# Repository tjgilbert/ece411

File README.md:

## ECE411 Practicum Project

**Project Focus:** Inductive Charging

**Team 10:** Jeff Brown, Katie Dahn, Tyler Gilbert, Jann Messer

*  [Project Wiki] (https://github.com/tjgilbert/ece411/wiki)

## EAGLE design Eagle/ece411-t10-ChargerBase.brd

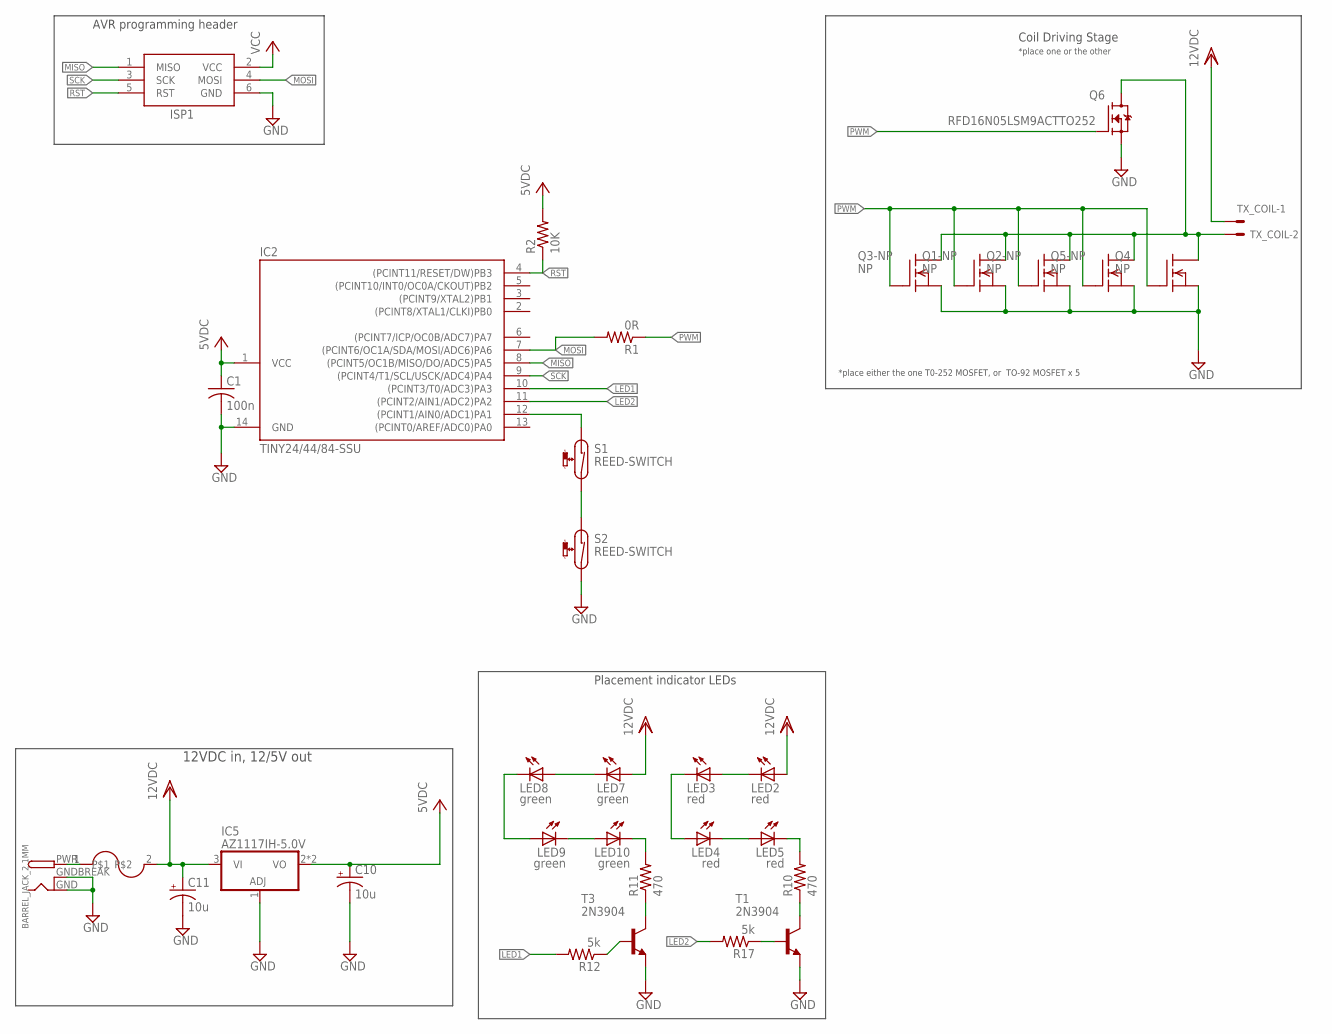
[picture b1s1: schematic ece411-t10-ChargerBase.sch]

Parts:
BARREL_JACK_2.1MM: DCBARRELPTH; DCJACK_2MM_PTH
C1: 100n; C0805
C10, C11: 10u; E2-5
IC2: TINY24/44/84-SSU; SOIC14
IC5: AZ1117IH-5.0V; SOT223
ISP1: AVRISP-6; AVRISP
LED2, LED3, LED4, LED5: red; CHIPLED_0805
LED7, LED8, LED9, LED10: green; CHIPLED_0805
Q1-NP, Q2-NP, Q3-NP, Q4, Q5-NP: NP; TO-92
Q6: RFD16N05LSM9ACTTO252; TO252
R1: 0R; R0805
R2: 10K; R0805
R10, R11: 470; R0805
R12, R17: 5k; R0805
S1, S2: REED-SWITCH; MK6-6
T1, T3: 2N3904; TO92
TX_COIL: 22-23-2021
U$1: LITTLEFUSE

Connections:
DRAIN: Q1-NP.3 (D), Q2-NP.3 (D), Q3-NP.3 (D), Q4.3 (D), Q5-NP.3 (D), Q6.3 (D), TX_COIL.2
GND: BARREL_JACK_2.1MM.GND, BARREL_JACK_2.1MM.GNDBREAK, C1.2, C10.-, C11.-, IC2.14 (GND), IC5.1 (ADJ), ISP1.6 (GND), Q1-NP.1 (S), Q2-NP.1 (S), Q3-NP.1 (S), Q4.1 (S), Q5-NP.1 (S), Q6.2 (S), S2.2, T1.3 (E), T3.3 (E)
LED1: IC2.10 ((PCINT3/T0/ADC3)PA3), R12.2
LED2: IC2.11 ((PCINT2/AIN1/ADC2)PA2), R17.2
MISO: IC2.8 ((PCINT5/OC1B/MISO/DO/ADC5)PA5), ISP1.1 (MISO)
MOSI: IC2.7 ((PCINT6/OC1A/SDA/MOSI/ADC6)PA6), ISP1.4 (MOSI), R1.2
unnamed: R11.1, T3.1 (C)
unnamed: LED10.C, R11.2
unnamed: BARREL_JACK_2.1MM.PWR, U$1.1
unnamed: R17.1, T1.2 (B)
unnamed: R10.1, T1.1 (C)
unnamed: LED5.C, R10.2
unnamed: LED2.C, LED3.A
unnamed: LED3.C, LED4.A
unnamed: LED4.C, LED5.A
unnamed: S1.2, S2.1
unnamed: LED7.C, LED8.A
unnamed: LED8.C, LED9.A
unnamed: LED9.C, LED10.A
unnamed: R12.1, T3.2 (B)
PIN12: IC2.12 ((PCINT1/AIN0/ADC1)PA1), S1.1
PWM: Q1-NP.2 (G), Q2-NP.2 (G), Q3-NP.2 (G), Q4.2 (G), Q5-NP.2 (G), Q6.1 (G), R1.1
RST: IC2.4 ((PCINT11/RESET/DW)PB3), ISP1.5 (RST), R2.1
SCK: IC2.9 ((PCINT4/T1/SCL/USCK/ADC4)PA4), ISP1.3 (SCK)
VCC: C1.1, C10.+, IC2.1 (VCC), IC5.2 (VO), IC5.4 (VO), ISP1.2 (VCC), R2.2
VDD: C11.+, IC5.3 (VI), LED2.A, LED7.A, TX_COIL.1, U$1.2

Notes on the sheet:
AVR programming header
12VDC in, 12/5V out
Coil Driving Stage
Placement indicator LEDs
*place one or the other
*place either the one T0-252 MOSFET, or TO-92 MOSFET x 5

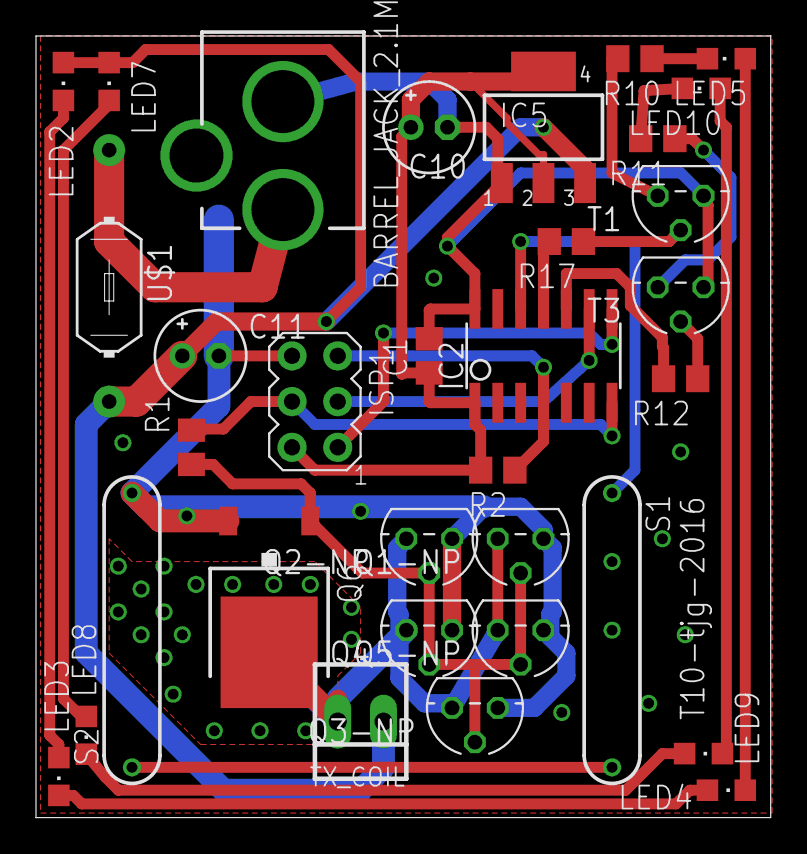
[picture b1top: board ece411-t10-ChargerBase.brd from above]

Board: 2 copper layers, 40.8 x 43.4 mm, 33 parts (0 on the bottom side), 26 nets.

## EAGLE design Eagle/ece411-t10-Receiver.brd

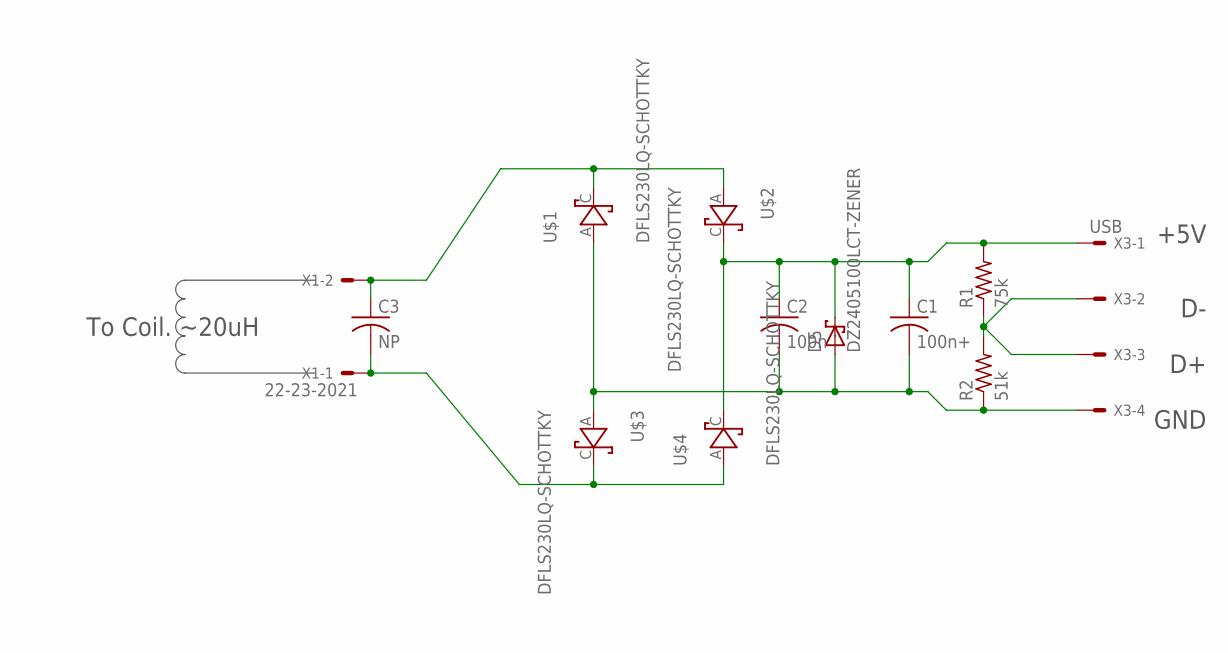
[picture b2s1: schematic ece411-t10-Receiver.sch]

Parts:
C1: 100n+; C0805
C2: 100n; C0805
C3: NP; C0805
D5: DZ2405100LCT-ZENER; ZENER_PWR_PKG
R1: 75k; R0805
R2: 51k; R0805
U$1, U$2, U$3, U$4: DFLS230LQ-SCHOTTKY; PWRDI123
X1: 22-23-2021
X3: USB; 22-23-2041

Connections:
5V: C1.1, C2.1, D5.C, R1.2, U$2.C, U$4.C, X3.1
GND: C1.2, C2.2, D5.A, R2.1, U$1.A, U$3.A, X3.4
unnamed: C3.1, U$1.C, U$2.A, X1.2
unnamed: C3.2, U$3.C, U$4.A, X1.1
unnamed: R1.1, R2.2, X3.2, X3.3

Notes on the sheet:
To Coil. ~20uH
+5V
GND

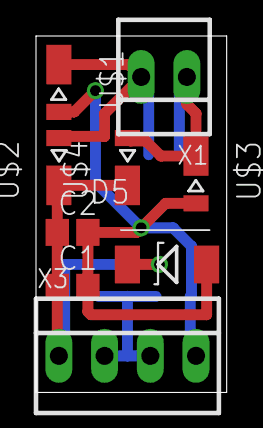
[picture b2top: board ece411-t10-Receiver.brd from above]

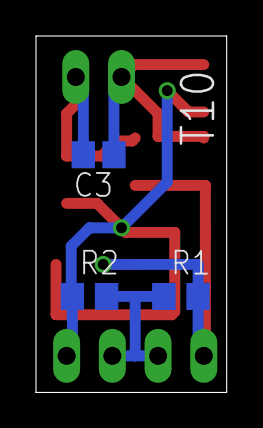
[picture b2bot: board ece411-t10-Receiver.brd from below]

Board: 2 copper layers, 10.6 x 19.8 mm, 12 parts (3 on the bottom side), 5 nets.

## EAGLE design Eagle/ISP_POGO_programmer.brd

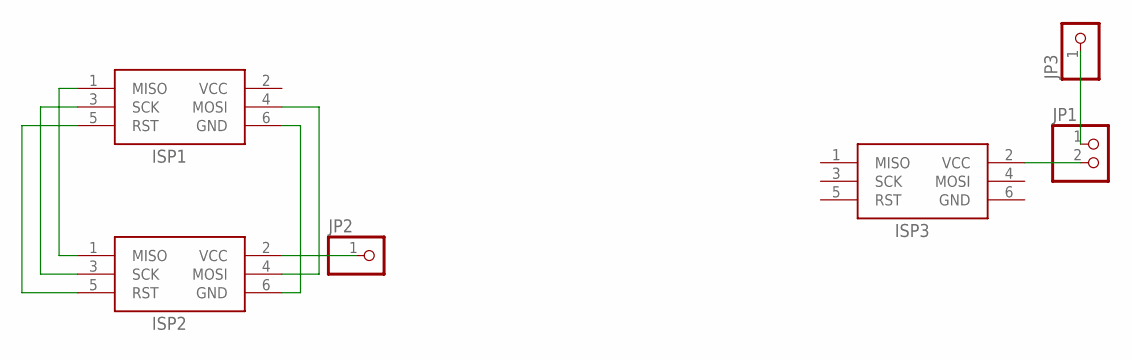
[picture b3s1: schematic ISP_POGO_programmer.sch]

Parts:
ISP1, ISP2, ISP3: AVRISP-6; AVRISP
JP1: PINHD-1X2; 1X02
JP2, JP3: PINHD-1X1; 1X01

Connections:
GND: ISP3.6 (GND)
unnamed: ISP1.1 (MISO), ISP2.1 (MISO)
unnamed: ISP1.3 (SCK), ISP2.3 (SCK)
unnamed: ISP1.5 (RST), ISP2.5 (RST)
unnamed: ISP1.6 (GND), ISP2.6 (GND)
unnamed: ISP1.4 (MOSI), ISP2.4 (MOSI)
unnamed: ISP3.2 (VCC), JP1.2
unnamed: JP1.1, JP3.1
unnamed: ISP2.2 (VCC), JP2.1
VCC: ISP1.2 (VCC)

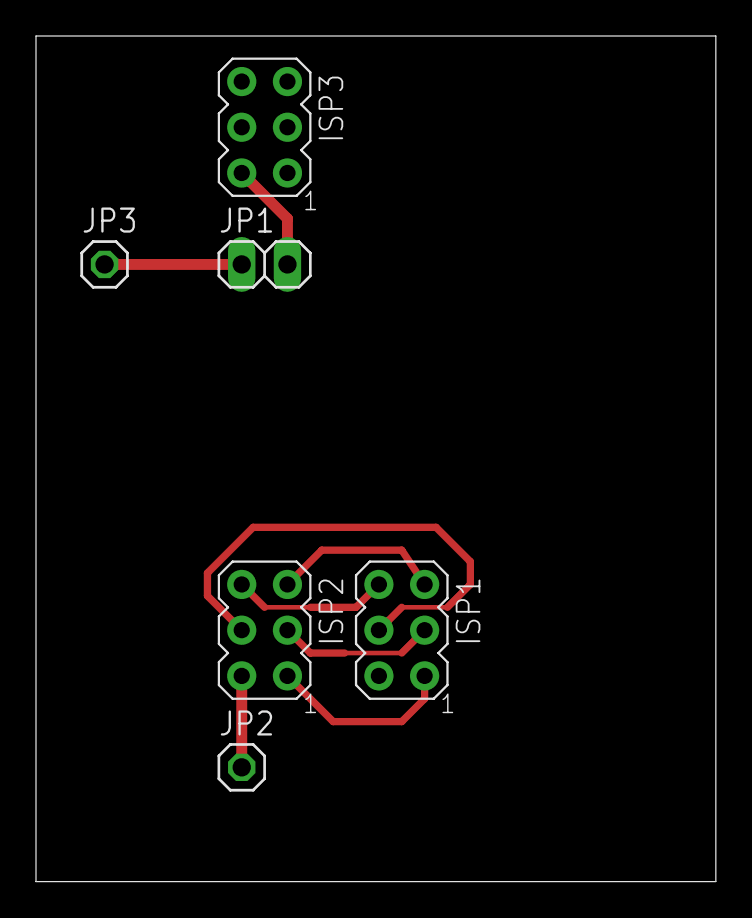
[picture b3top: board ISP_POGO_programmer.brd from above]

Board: 2 copper layers, 37.8 x 47.0 mm, 6 parts (0 on the bottom side), 8 nets.

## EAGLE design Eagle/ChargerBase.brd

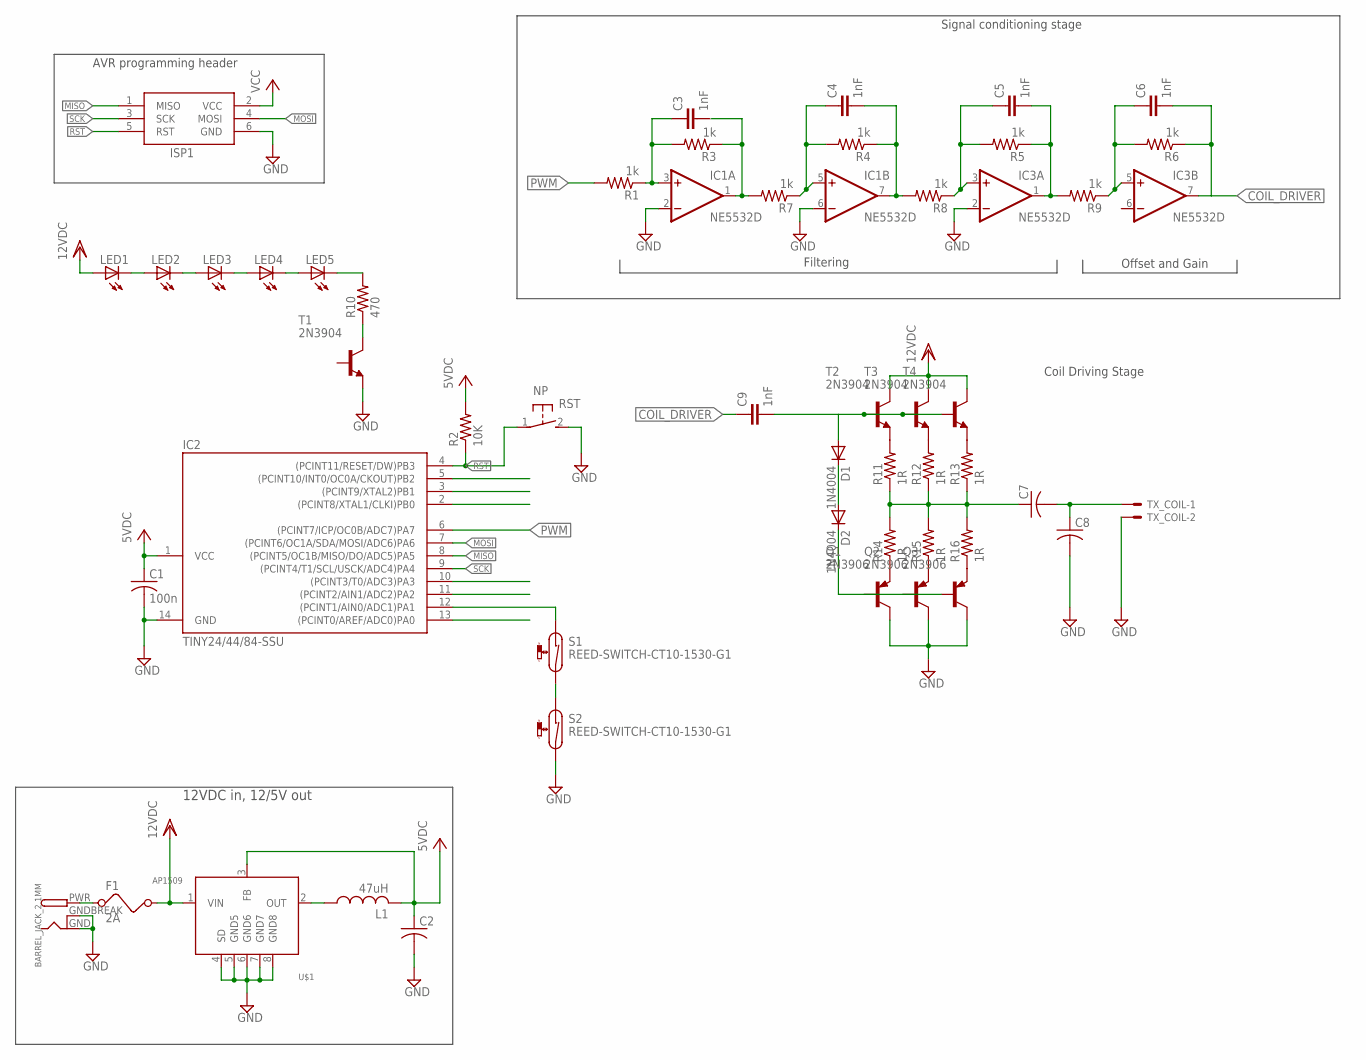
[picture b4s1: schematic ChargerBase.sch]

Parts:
BARREL_JACK_2.1MM: DCBARRELPTH; DCJACK_2MM_PTH
C1: 100n; C0805
C2: C-US025-040X050; C025-040X050
C3, C4, C5, C6, C9: 1nF; C0805
C7, C8: C-US050-025X075; C050-025X075
D1, D2: 1N4004; DO41-10
F1: 2A; FUSE
IC1, IC3: NE5532D; SO08
IC2: TINY24/44/84-SSU; SOIC14
ISP1: AVRISP-6; AVRISP
L1: 47uH; 0207/7
LED1, LED2, LED3, LED4, LED5: LEDCHIPLED_0805; CHIPLED_0805
NP: RST; DTSM-3
Q1, Q2, Q3: 2N3906; TO92
R1, R3, R4, R5, R6, R7, R8, R9: 1k; R0805
R2: 10K; R0805
R10: 470; R0805
R11, R12, R13, R14, R15, R16: 1R; R0805
S1, S2: REED-SWITCH-CT10-1530-G1; CT10-G1
T1, T2, T3, T4: 2N3904; TO92
TX_COIL: 22-23-2021
U$1: AP1509; SOP08

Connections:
COIL_DRIVER: C6.2, C9.1, IC3.7 (OUT), R6.1
GND: BARREL_JACK_2.1MM.GND, BARREL_JACK_2.1MM.GNDBREAK, C1.2, C2.2, C8.2, IC1.2 (-IN), IC1.6 (-IN), IC2.14 (GND), IC3.2 (-IN), ISP1.6 (GND), NP.2, Q1.1 (C), Q2.1 (C), Q3.1 (C), S2.2, T1.3 (E), TX_COIL.2, U$1.4 (SD), U$1.5 (GND5), U$1.6 (GND6), U$1.7 (GND7), U$1.8 (GND8)
MISO: IC2.8 ((PCINT5/OC1B/MISO/DO/ADC5)PA5), ISP1.1 (MISO)
MOSI: IC2.7 ((PCINT6/OC1A/SDA/MOSI/ADC6)PA6), ISP1.4 (MOSI)
unnamed: C3.1, IC1.3 (+IN), R1.1, R3.2
unnamed: L1.1, U$1.2 (OUT)
unnamed: R11.2, T2.3 (E)
unnamed: BARREL_JACK_2.1MM.PWR, F1.1
unnamed: IC1.1 (OUT), R3.1, R7.2
unnamed: C4.1, IC1.5 (+IN), R4.2, R7.1
unnamed: C4.2, IC1.7 (OUT), R4.1, R8.2
unnamed: C5.1, IC3.3 (+IN), R5.2, R8.1
unnamed: C5.2, IC3.1 (OUT), R5.1, R9.2
unnamed: C6.1, IC3.5 (+IN), R6.2, R9.1
unnamed: R12.2, T3.3 (E)
unnamed: LED1.C, LED2.A
unnamed: LED2.C, LED3.A
unnamed: LED3.C, LED4.A
unnamed: LED4.C, LED5.A
unnamed: LED5.C, R10.2
unnamed: S1.2, S2.1
unnamed: R13.2, T4.3 (E)
unnamed: Q1.3 (E), R14.1
unnamed: Q2.3 (E), R15.1
unnamed: Q3.3 (E), R16.1
unnamed: C7.1, R11.1, R12.1, R13.1, R14.2, R15.2, R16.2
unnamed: C9.2, D1.A, T2.2 (B), T3.2 (B), T4.2 (B)
unnamed: D1.C, D2.A
unnamed: C7.2, C8.1, TX_COIL.1
unnamed: D2.C, Q1.2 (B), Q2.2 (B), Q3.2 (B)
PIN10: IC2.10 ((PCINT3/T0/ADC3)PA3)
PIN11: IC2.11 ((PCINT2/AIN1/ADC2)PA2)
PIN12: IC2.12 ((PCINT1/AIN0/ADC1)PA1), S1.1
PIN13: IC2.13 ((PCINT0/AREF/ADC0)PA0)
PWM: IC2.6 ((PCINT7/ICP/OC0B/ADC7)PA7), R1.2
RST: IC2.4 ((PCINT11/RESET/DW)PB3), ISP1.5 (RST), NP.1, R2.1
SCK: IC2.9 ((PCINT4/T1/SCL/USCK/ADC4)PA4), ISP1.3 (SCK)
V+: IC1.8 (V+), IC3.8 (V+)
V-: IC1.4 (V-), IC3.4 (V-)
VCC: C1.1, C2.1, IC2.1 (VCC), ISP1.2 (VCC), L1.2, R2.2, U$1.3 (FB)
VDD: F1.2, LED1.A, T2.1 (C), T3.1 (C), T4.1 (C), U$1.1 (VIN)

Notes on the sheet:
AVR programming header
12VDC in, 12/5V out
Filtering
Offset and Gain
Coil Driving Stage
Signal conditioning stage

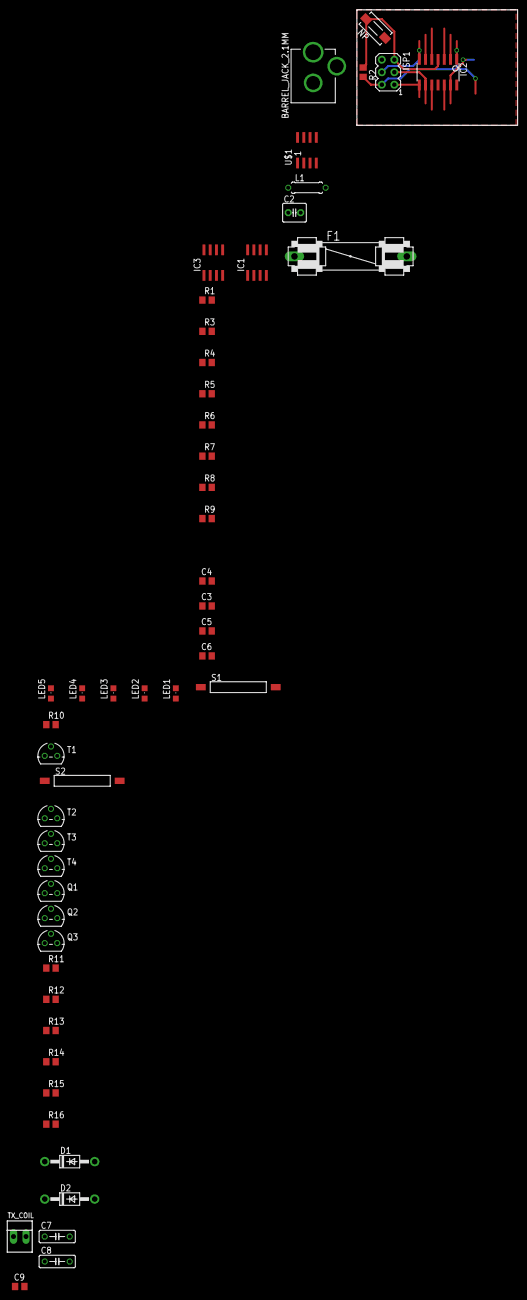
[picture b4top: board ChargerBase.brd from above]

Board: 2 copper layers, 32.7 x 23.5 mm, 51 parts (1 on the bottom side), 38 nets.

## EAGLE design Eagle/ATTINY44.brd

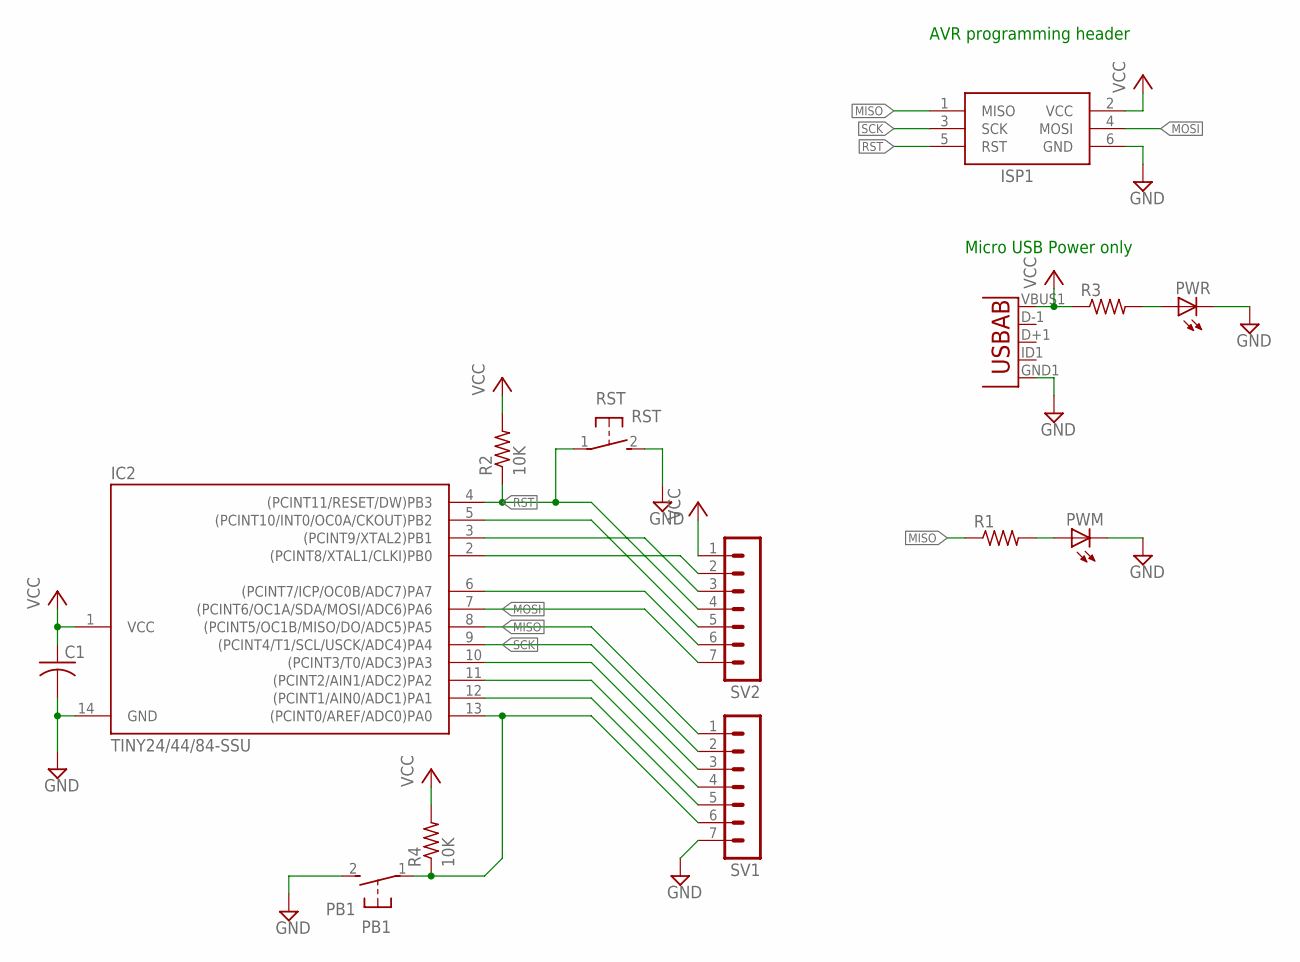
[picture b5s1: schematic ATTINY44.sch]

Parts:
C1: C-USC0805; C0805
IC2: TINY24/44/84-SSU; SOIC14
ISP1: AVRISP-6; AVRISP
PB1: PB1; DTSM-3
PWM: LEDCHIPLED_0805; CHIPLED_0805
PWR: LEDCHIPLED_0805; CHIPLED_0805
R1, R3: R-US_R0805; R0805
R2, R4: 10K; R0805
RST: RST; DTSM-3
SV1, SV2: MA07-1
U1: USB""; USB-MICRO-SMD

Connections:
GND: C1.2, IC2.14 (GND), ISP1.6 (GND), PB1.2, PWM.C, PWR.C, RST.2, SV1.7, U1.GND1 (GND)
MISO: IC2.8 ((PCINT5/OC1B/MISO/DO/ADC5)PA5), ISP1.1 (MISO), R1.1, SV1.1
MOSI: IC2.7 ((PCINT6/OC1A/SDA/MOSI/ADC6)PA6), ISP1.4 (MOSI), SV2.7
unnamed: PWR.A, R3.2
unnamed: PWM.A, R1.2
unnamed: IC2.2 ((PCINT8/XTAL1/CLKI)PB0), SV2.2
unnamed: IC2.3 ((PCINT9/XTAL2)PB1), SV2.3
unnamed: IC2.5 ((PCINT10/INT0/OC0A/CKOUT)PB2), SV2.5
unnamed: IC2.6 ((PCINT7/ICP/OC0B/ADC7)PA7), SV2.6
PIN10: IC2.10 ((PCINT3/T0/ADC3)PA3), SV1.3
PIN11: IC2.11 ((PCINT2/AIN1/ADC2)PA2), SV1.4
PIN12: IC2.12 ((PCINT1/AIN0/ADC1)PA1), SV1.5
PIN13: IC2.13 ((PCINT0/AREF/ADC0)PA0), PB1.1, R4.1, SV1.6
RST: IC2.4 ((PCINT11/RESET/DW)PB3), ISP1.5 (RST), R2.1, RST.1, SV2.4
SCK: IC2.9 ((PCINT4/T1/SCL/USCK/ADC4)PA4), ISP1.3 (SCK), SV1.2
VCC: C1.1, IC2.1 (VCC), ISP1.2 (VCC), R2.2, R3.1, R4.2, SV2.1, U1.VBUS1 (VBUS)

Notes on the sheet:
AVR programming header
Micro USB Power only

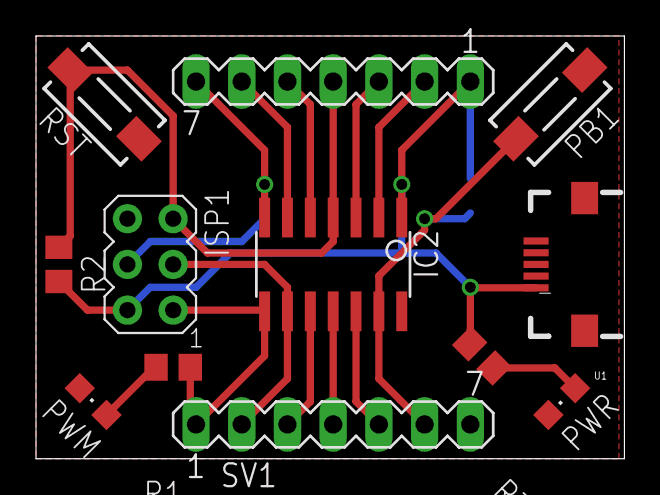
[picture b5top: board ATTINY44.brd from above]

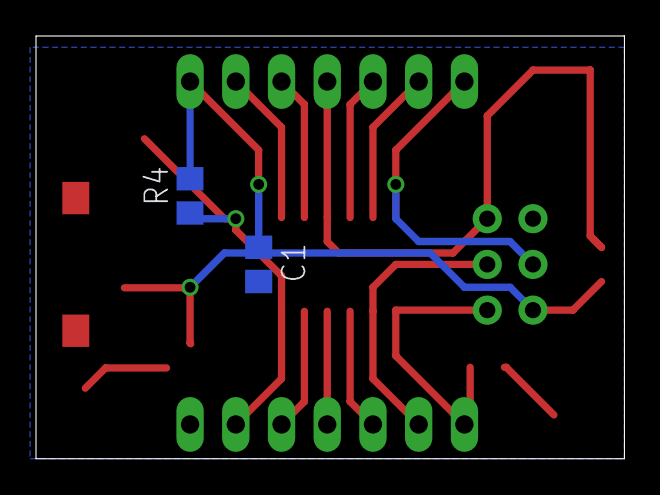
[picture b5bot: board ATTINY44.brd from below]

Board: 2 copper layers, 32.7 x 23.5 mm, 14 parts (2 on the bottom side), 16 nets.

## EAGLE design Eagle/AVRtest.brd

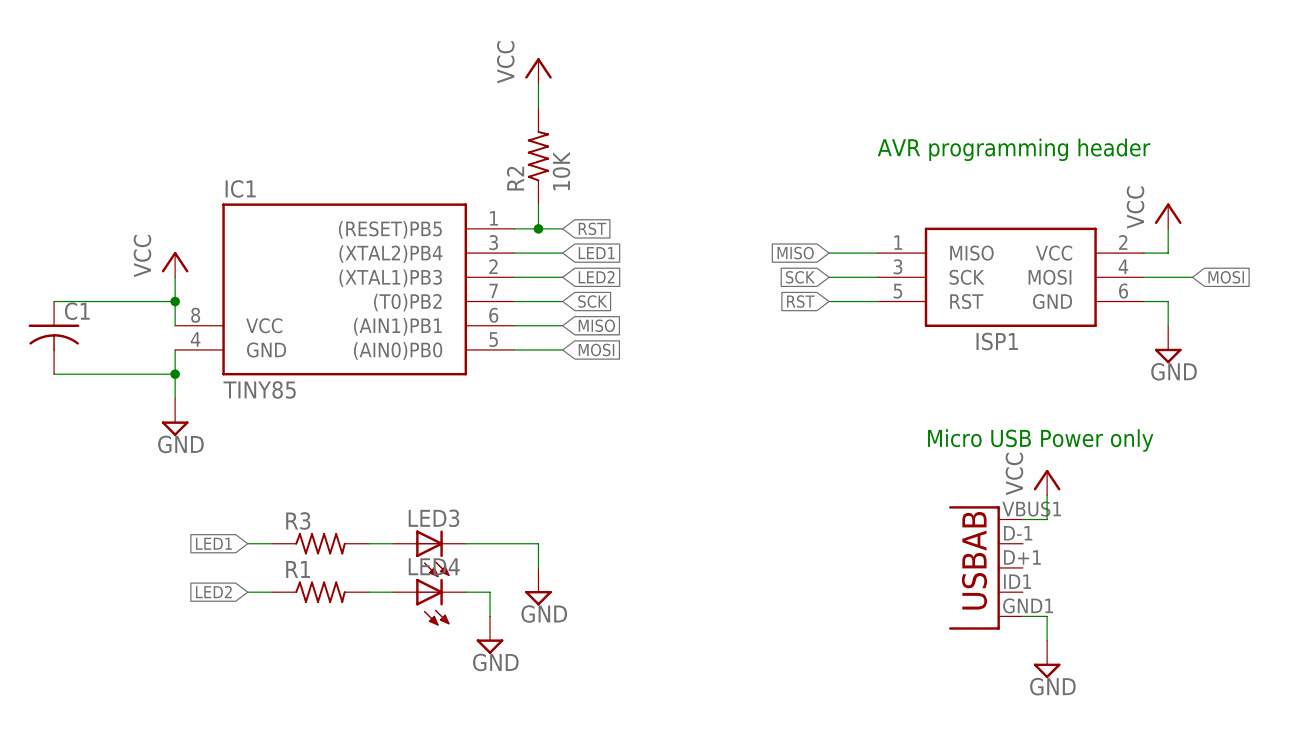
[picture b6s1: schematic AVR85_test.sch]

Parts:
C1: C-USC0805; C0805
IC1: TINY85; SOIC8
ISP1: AVRISP-6; AVRISP
LED3, LED4: LEDCHIPLED_0805; CHIPLED_0805
R1, R3: R-US_R0805; R0805
R2: 10K; R0805
U1: USB""; USB-MICRO-SMD

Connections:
GND: C1.2, IC1.4 (GND), ISP1.6 (GND), LED3.C, LED4.C, U1.GND1 (GND)
LED1: IC1.3 ((XTAL2)PB4), R3.1
LED2: IC1.2 ((XTAL1)PB3), R1.1
MISO: IC1.6 ((AIN1)PB1), ISP1.1 (MISO)
MOSI: IC1.5 ((AIN0)PB0), ISP1.4 (MOSI)
unnamed: LED3.A, R3.2
unnamed: LED4.A, R1.2
RST: IC1.1 ((RESET)PB5), ISP1.5 (RST), R2.1
SCK: IC1.7 ((T0)PB2), ISP1.3 (SCK)
VCC: C1.1, IC1.8 (VCC), ISP1.2 (VCC), R2.2, U1.VBUS1 (VBUS)

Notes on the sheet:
AVR programming header
Micro USB Power only

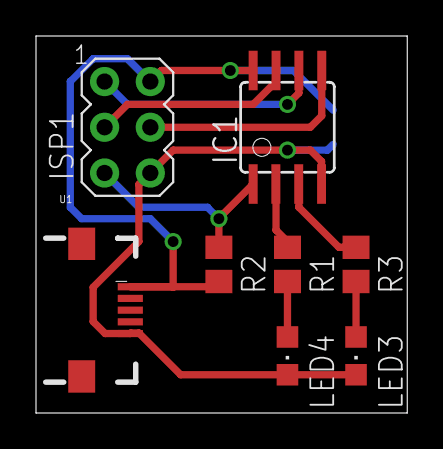
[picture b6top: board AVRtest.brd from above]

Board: 2 copper layers, 20.6 x 20.9 mm, 9 parts (1 on the bottom side), 10 nets.

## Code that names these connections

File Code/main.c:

#include <stdio.h>
#include <avr/io.h>
#include <avr/interrupt.h>
#include <util/delay.h>
#include <avr/power.h>

void initIO(void) {
/*       PDIP/SOIC Pinout:
                                VCC|1 14|GND
            (PCINT8/XTAL1/CLKI) PB0|2 13|PA0 (ADC0/AREF/PCINT0)
                 (PCINT9/XTAL2) PB1|3 12|PA1 (ADC1/AIN0/PCINT1)
             (PCINT11/RESET/dW) PB3|4 11|PA2 (ADC2/AIN1/PCINT2)
      (PCINT10/INT0/OC0A/CKOUT) PB2|5 10|PA3 (ADC3/T0/PCINT3)
         (PCINT7/ICP/OC0B/ADC7) PA7|6  9|PA4 (ADC4/USCK/SCL/T1/PCINT4)
 (PCINT6/OC1A/SDA/MOSI/DI/ADC6) PA6|7  8|PA5 (ADC5/DO/MISO/OC1B/PCINT5)
*/
    
 //Initial setup:
 // MCUCR = 0x40; // Uncomment to disable internal pull ups
    DDRA =  0b11111111; //Port A data direction register [DDA7:DDA0] (0=input 1=output)
    DDRB =  0xFF; //Port B data direction register [DDB3:DDB0] (0=input 1=output)
    PORTA = 0b00000000; //Port A data register [PORTA7:PORTA0]
    PORTB = 0b00000000; //Port B data register [PORTA3:PORTB0]
    
    
//PWM SETUP
    
    OSCCAL = 0x7F; // set internal oscilator frequency. The two values overlap, ie. 0x7F > 0x80
    clock_prescale_set(0);  // default is /8.. (0) = /1 , (1)= /2, (8)=/256
    
    //DDRA|=(1<<PA6);
    
    TCCR1A = _BV(COM1A1) | _BV(WGM11);     //TCCR1A = COM1A1 COM1A0 COM1B1 COM1B0 – – WGM11 WGM10
   
    TCCR1B = _BV(CS10) | _BV(WGM12) | _BV(WGM13);
        ICR1 = 80;
        OCR1A = 40;
        OCR1B = 40;
    
    
    
    TCCR0A = _BV(COM0B1) /*| _BV(COM0B0)*/ | _BV(WGM02)|_BV(WGM01) | _BV(WGM00);
    
    TCCR0B = _BV(CS00) ; //No prescaling - toggle mode?
    
    OCR0A =10;
    OCR0B = 50;
}

int main(void) {
    
	initIO();

    
	while (1) {
	/*
        do nothing
    */
     }
	return 0; // never reached
}

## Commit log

2016-10-12 Added subfolders
2016-10-12 Revert "Added subfolders"
    This reverts commit 49b2c9061165242376cadfb0a99d3f012eb89102.
2016-10-12 Added AVR test board schematics
2016-10-16 Commit Test
2016-10-16 Added ATTINY44 breakout board
2016-10-17 Waveform and FFT from inductive tap on transmit coil.
2016-10-17 Test setup, reference photo
2016-10-18 Made folders
2016-10-23 added code section
2016-10-23 Added some initialization code
2016-10-23 deleted eagle autosave files and added to .gitignore
2016-10-24 uploaded requirements document
2016-10-24 Completed PDS
2016-10-24 Uploaded PDS pdf
2016-10-25 Uploaded HW3 V1.2
2016-10-25 PDS rev 1.3
2016-10-25 Pushed final copy of PDS + source
2016-10-25 Create ATTiny85 Programming
    These are some useful reference documents for the ATTiny85
2016-10-26 Update ATTiny85 Programming
2016-10-31 Added library information for ATTiny44 and ATTiny85 master and slave
2016-11-01 Update and rename ATTiny85 Programming to ATTiny Programming
2016-11-01 Update ATTiny Programming
2016-11-02 Updated uC code
2016-11-02 Updated schematic
2016-11-03 Create LTspice schematics- Receiver
2016-11-03 Uploaded schematics
2016-11-04 Moved breakout test boards to own folder
2016-11-04 deleted corrupt file
2016-11-04 renamed file
2016-11-04 Rename Receiver.sch to T10_Receiver.sch
2016-11-04 Rename ChargerBase.sch to T10_ChargerBase.sch
2016-11-06 Add files via upload
    Work in progress copy of the work breakdown schedule. Started in MS Project '16
2016-11-08 Add files via upload
    Mark 2 of Work Breakdown Schedule
2016-11-08 Add files via upload
    Mark2
2016-11-08 Add files via upload
    Version 3 of WBS
2016-11-08 Add files via upload
    Added second resource tab, added aesthetics and finalization
2016-11-08 Create WBS
2016-11-08 changed pwm mode
2016-11-08 Moved schedule to project docs folder
2016-11-08 system overview
2016-11-10 Board files and update uC program
2016-11-10 Complementary Symmetry Amplifier Output Stage Spice Schematic
    Spice Schematic of Comp Sym Output stage as built and tested in the lab. The DC node voltages were pretty close to the real thing, I didn't measure the currents.
2016-11-10 Rename T10_ChargerBase.brd to ece411-t10-ChargerBase.brd
2016-11-10 Rename T10_Receiver.sch to ece411-t10-Receiver.sch
2016-11-10 Rename T10_Receiver.brd to ece411-t10-Receiver.brd
2016-11-10 Rename T10_ChargerBase.sch to ece411-t10-ChargerBase.sch
2016-11-11 Create Notes
    Lab Tests
2016-11-11 Add files via upload
    MOSFET Experiments, see MOSFET_Notes for description of setup
2016-11-11 Rename Notes.txt to MOSFET_Notes.txt
2016-11-12 Add files via upload
    This schematic is the one I am currently working on, in the simulation I am driving a parallel combination of a 47nF cap with 22uH inductor, their resonant frequency is 125kHz. I built and tested thi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
    I'm currently working to get the output bigger than a few tens of mV with the load hooked up. I am going to simulate next instead of driving the inductor and cap, driving the output stage. I'm going 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
    Please play around with feeding this filtered signal into different output driving stages.
    I built the circuit using the
2016-11-16 Boards + schematics rev2
2016-11-16 changed silkscreen
2016-11-16 deleted empty file
2016-11-16 cleaned up schematic. fixed minor ERC error
2016-11-24 Datasheet MOSFET
    datasheet
2016-11-24 Add files via upload
    Revision 2 of 5.2.1 after breaking 5.2.2 into a separate test
2016-11-24 Add files via upload
    Changed test case pdf to image file for in line addition to test wiki
2016-11-24 Add files via upload
    5.2.1 and 5.2.2 were split in to two tests late last night. Adjusting test case forms to match the change
2016-12-02 IO working on program
2016-12-03 Create ppt
2016-12-03 Powerpoint for final presentation
2016-12-03 Add files via upload
    I made some edits and added a few things
    I have a question about the calculations page (Slide 12): I wrote the question on the slide as well so we need to make sure to edit it out when we decide what we are doing.
    What calculations did we do? I'm aware that we made measurements in order to determine characteristics of the various coils
2016-12-07 Add files via upload
    Work in Progress
2016-12-08 clean up
